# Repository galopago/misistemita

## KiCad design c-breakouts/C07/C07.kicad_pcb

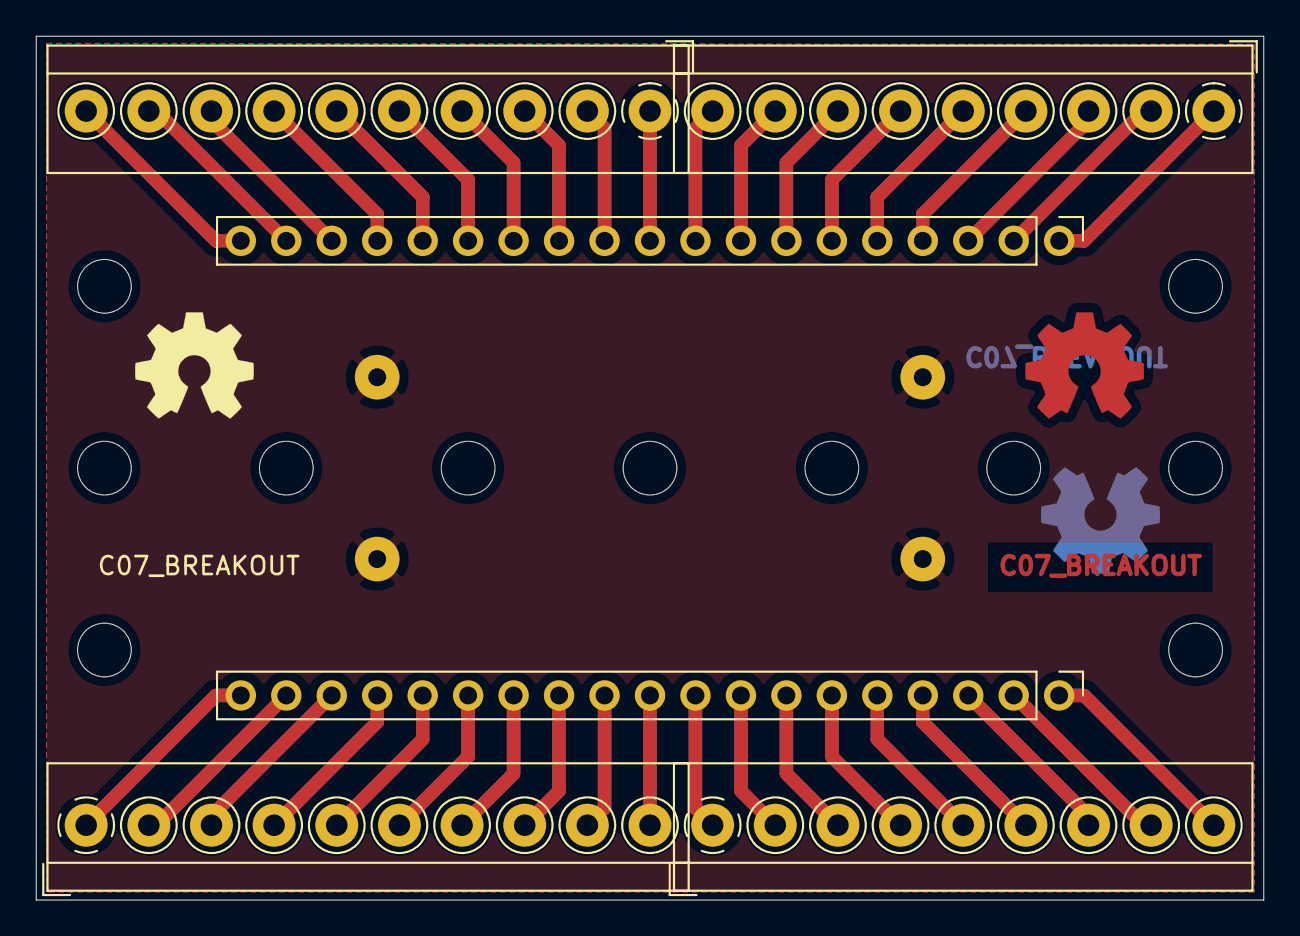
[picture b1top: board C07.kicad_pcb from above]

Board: 2 copper layers, 68.6 x 48.3 mm, 21 parts (0 on the bottom side), 39 nets.

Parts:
HB0, HB6: MountingHole; MountingHole_3mm
HC0, HC1, HC2, HC3, HC4, HC5, HC6: MountingHole; MountingHole_3mm
HD0, HD6: MountingHole; MountingHole_3mm
J0, J1, J2, J3: Conn_01x01_Male; SolderWirePad_1x01_Drill1mm
J4, J6: Conn_01x10_Female; TerminalBlock_4Ucon_1x10_P3.50mm_Horizontal
J5, J7: Conn_01x09_Female; TerminalBlock_4Ucon_1x09_P3.50mm_Horizontal
J8, J9: Conn_01x19_Female; PinHeader_1x19_P2.54mm_Vertical

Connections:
unnamed: J0.1, J1.1, J2.1, J3.1
unnamed: J4.1, J8.10
unnamed: J4.2, J8.11
unnamed: J4.3, J8.12
unnamed: J4.4, J8.13
unnamed: J4.5, J8.14
unnamed: J4.6, J8.15
unnamed: J4.7, J8.16
unnamed: J4.8, J8.17
unnamed: J4.9, J8.18
unnamed: J4.10, J8.19
unnamed: J5.1, J8.1
unnamed: J5.2, J8.2
unnamed: J5.3, J8.3
unnamed: J5.4, J8.4
unnamed: J5.5, J8.5
unnamed: J5.6, J8.6
unnamed: J5.7, J8.7
unnamed: J5.8, J8.8
unnamed: J5.9, J8.9
unnamed: J6.1, J9.19
unnamed: J6.2, J9.18
unnamed: J6.3, J9.17
unnamed: J6.4, J9.16
unnamed: J6.5, J9.15
unnamed: J6.6, J9.14
unnamed: J6.7, J9.13
unnamed: J6.8, J9.12
unnamed: J6.9, J9.11
unnamed: J6.10, J9.10
unnamed: J7.1, J9.9
unnamed: J7.2, J9.8
unnamed: J7.3, J9.7
unnamed: J7.4, J9.6
unnamed: J7.5, J9.5
unnamed: J7.6, J9.4
unnamed: J7.7, J9.3
unnamed: J7.8, J9.2
unnamed: J7.9, J9.1

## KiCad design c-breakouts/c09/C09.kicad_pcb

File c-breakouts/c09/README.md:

# Breakout for USB A female connected to a 3.5 mm pitch screw terminals (power terminals), 4 holes 10.16 mm spaced, for mounting onto the backplate.

Breakout for USB A female connected to a 3.5 mm pitch screw terminals (power terminals), 4 holes 10.16 mm spaced, for mounting onto the backplate. Useful to power modules that only have USB connector for power, but no header pins. (Using a suitable cable)

Bare single PCB                              |Panelized PCB                              |
---------------------------------------------|-------------------------------------------|
 | |

Connectors installed                         |Set attached to a 10.16 pitch backplate    |
---------------------------------------------|-------------------------------------------|
 | |

## Usage example #1

ESP32 connected to a LiFePo4 charger to send a message when charging ends. For this example the module is powered from the USB connector, therefore a breakout is needed.

Components required                                 |Ready to enclose                                 |
----------------------------------------------------|-------------------------------------------------|
||

Installed in box                             |Lid Closed                                           |
---------------------------------------------|-----------------------------------------------------|
||

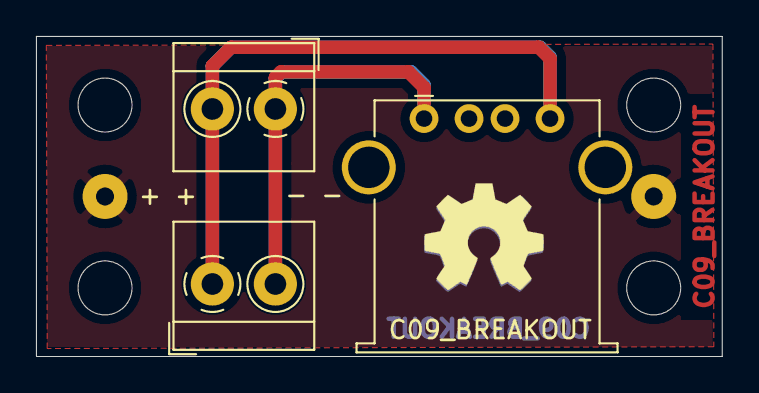
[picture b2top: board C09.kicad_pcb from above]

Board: 2 copper layers, 38.1 x 17.8 mm, 9 parts (0 on the bottom side), 3 nets.

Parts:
HA0, HA3: MountingHole; MountingHole_3mm
HB0, HB3: MountingHole; MountingHole_3mm
J0, J1: Conn_01x01_Male; SolderWirePad_1x01_Drill1mm
J4: USB_A; USB_A_Stewart_SS-52100-001_Horizontal
J5, J6: Conn_01x02_Female; TerminalBlock_4Ucon_1x02_P3.50mm_Horizontal

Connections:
unnamed: J0.1, J1.1
unnamed: J4.1, J5.1, J6.2
unnamed: J4.4, J5.2, J6.1

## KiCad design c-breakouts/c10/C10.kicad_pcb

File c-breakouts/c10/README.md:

# Breakout for I2C 0.96" OLED Display, 6 holes 10.16 mm spaced, for mounting onto the backplate.

Breakout for I2C 0.96" OLED Display, 6 holes 10.16 mm spaced, for mounting onto the backplate. Also suitable for other I2C 4-pin modules.

Bare single PCB                              |Panelized PCB                              |
---------------------------------------------|-------------------------------------------|
 | |

Connectors installed                         |Module and breakboard                      |
---------------------------------------------|-------------------------------------------|
 | |

Module attached to breakboard                |Set attached to a 10.16 pitch backplate    |
---------------------------------------------|-------------------------------------------|
 | |

## Usage example #1

ESP32 WiFi temperature probe with local display, Powered by 5V

Components required                                 |Ready to enclose                                 |
----------------------------------------------------|-------------------------------------------------|
||

Installed in box                             |Lid Closed                                       |
---------------------------------------------|-------------------------------------------------|
||

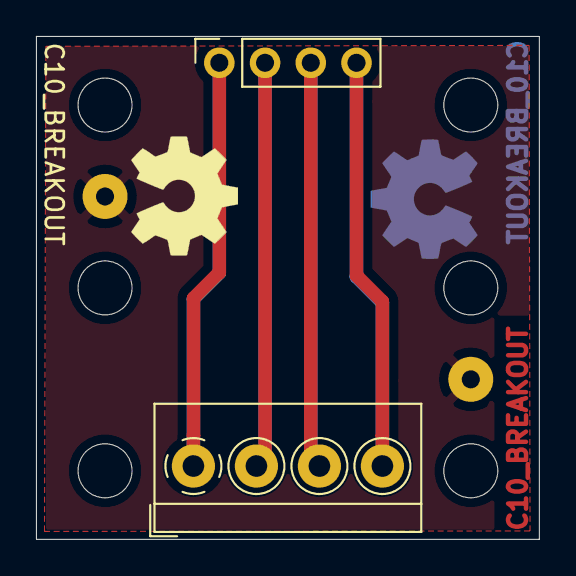
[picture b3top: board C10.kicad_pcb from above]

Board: 2 copper layers, 27.9 x 27.9 mm, 10 parts (0 on the bottom side), 5 nets.

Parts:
HA0, HA2: MountingHole; MountingHole_3mm
HB0, HB2: MountingHole; MountingHole_3mm
HC0, HC2: MountingHole; MountingHole_3mm
J0, J1: Conn_01x01_Male; SolderWirePad_1x01_Drill1mm
J4: Conn_01x04_Female; PinSocket_1x04_P2.54mm_Vertical
J5: Conn_01x04_Female; TerminalBlock_4Ucon_1x04_P3.50mm_Horizontal

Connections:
unnamed: J0.1, J1.1
unnamed: J4.1, J5.1
unnamed: J4.2, J5.2
unnamed: J4.3, J5.3
unnamed: J4.4, J5.4

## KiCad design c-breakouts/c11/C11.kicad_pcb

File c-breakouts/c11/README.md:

# Breakboard for Raspberry Pi Pico, 4 holes 10.16 mm spaced, for mounting onto the backplate

Breakboard for Raspberry Pi Pico, 4 holes 10.16 mm spaced, for mounting onto the backplate. All pins routed to 3.5 mm pitch screw terminals

Bare single PCB                              |Panelized PCB                              |
---------------------------------------------|-------------------------------------------|
 | |

Connectors installed                         |Module and breakboard                      |
---------------------------------------------|-------------------------------------------|
 | |

Module attached to breakboard                |Set attached to a 10.16 pitch backplate    |
---------------------------------------------|-------------------------------------------|
 | |

## Usage example #1

Raspberry Pi Pico based USB foot pedal. Detachable external pedals and USB cable.

Module on backplate                                 |Ready to enclose                                 |
----------------------------------------------------|-------------------------------------------------|
||

Installed in box                             |Lid Closed                                       |
---------------------------------------------|-------------------------------------------------|
||

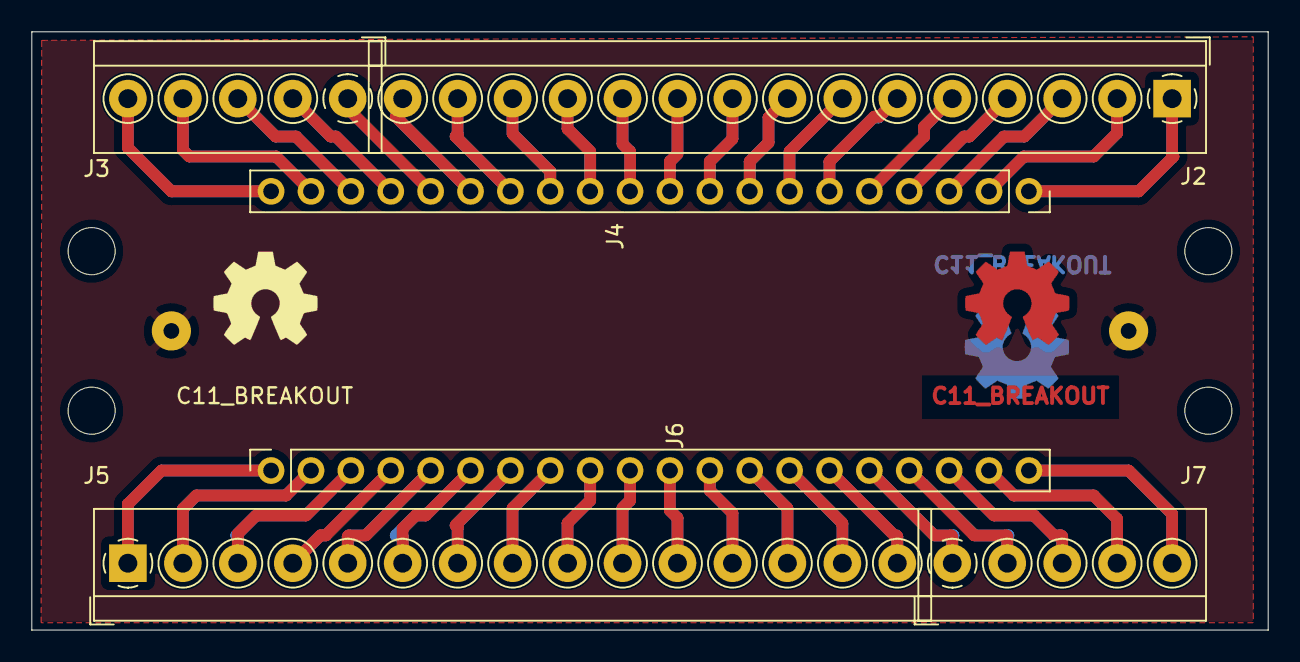
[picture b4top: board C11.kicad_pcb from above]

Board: 2 copper layers, 78.7 x 38.1 mm, 12 parts (0 on the bottom side), 41 nets.

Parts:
HB0, HB5: MountingHole; MountingHole_3mm
HC0, HC5: MountingHole; MountingHole_3mm
J0, J1: Conn_01x01_Male; SolderWirePad_1x01_Drill1mm
J2, J5: Conn_01x15_Female; TerminalBlock_4Ucon_1x15_P3.50mm_Horizontal
J3, J7: Conn_01x05_Female; TerminalBlock_4Ucon_1x05_P3.50mm_Horizontal
J4, J6: Conn_01x20_Female; PinSocket_1x20_P2.54mm_Vertical

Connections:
unnamed: J0.1, J1.1
unnamed: J2.1, J4.1
unnamed: J2.2, J4.2
unnamed: J2.3, J4.3
unnamed: J2.4, J4.4
unnamed: J2.5, J4.5
unnamed: J2.6, J4.6
unnamed: J2.7, J4.7
unnamed: J2.8, J4.8
unnamed: J2.9, J4.9
unnamed: J2.10, J4.10
unnamed: J2.11, J4.11
unnamed: J2.12, J4.12
unnamed: J2.13, J4.13
unnamed: J2.14, J4.14
unnamed: J2.15, J4.15
unnamed: J3.1, J4.16
unnamed: J3.2, J4.17
unnamed: J3.3, J4.18
unnamed: J3.4, J4.19
unnamed: J3.5, J4.20
unnamed: J5.1, J6.1
unnamed: J5.2, J6.2
unnamed: J5.3, J6.3
unnamed: J5.4, J6.4
unnamed: J5.5, J6.5
unnamed: J5.6, J6.6
unnamed: J5.7, J6.7
unnamed: J5.8, J6.8
unnamed: J5.9, J6.9
unnamed: J5.10, J6.10
unnamed: J5.11, J6.11
unnamed: J5.12, J6.12
unnamed: J5.13, J6.13
unnamed: J5.14, J6.14
unnamed: J5.15, J6.15
unnamed: J6.16, J7.1
unnamed: J6.17, J7.2
unnamed: J6.18, J7.3
unnamed: J6.19, J7.4
unnamed: J6.20, J7.5

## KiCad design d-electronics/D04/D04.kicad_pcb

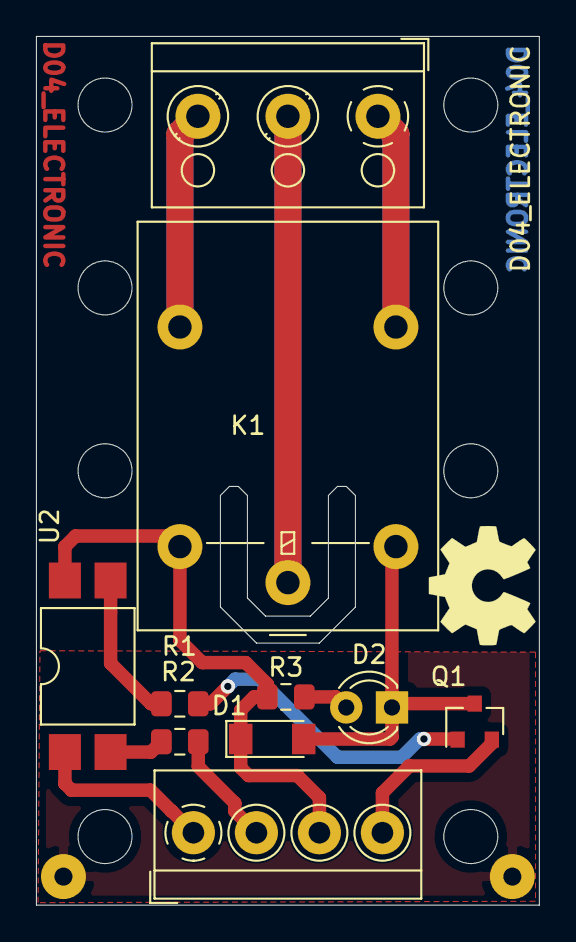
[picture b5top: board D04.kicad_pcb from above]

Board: 2 copper layers, 27.9 x 48.3 mm, 20 parts (0 on the bottom side), 13 nets.

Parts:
D1: LL4148; D_MiniMELF
D2: LED; LED_D3.0mm
HA0, HA2: MountingHole; MountingHole_3mm
HB0, HB2: MountingHole; MountingHole_3mm
HC0, HC2: MountingHole; MountingHole_3mm
HE0, HE2: MountingHole; MountingHole_3mm
J0, J1: Conn_01x01_Male; SolderWirePad_1x01_Drill1mm
J4: Conn_01x03_Female; TerminalBlock_RND_205-00002_1x03_P5.00mm_Horizontal
J5: Conn_01x04_Female; TerminalBlock_4Ucon_1x04_P3.50mm_Horizontal
K1: G5LE-1; Relay_SPDT_Omron-G5LE-1
Q1: MMBT3904; SOT-23
R1, R2, R3: R; R_0805_2012Metric_Pad1.15x1.40mm_HandSolder
U2: LTV-817S; SMDIP-4_W9.53mm

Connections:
unnamed: D1.1, J5.3, K1.5, R3.1, U2.4
unnamed: D1.2, D2.1, K1.2, Q1.3
unnamed: D2.2, R3.2
unnamed: J0.1, J1.1
unnamed: J4.1, K1.3
unnamed: J4.2, K1.1
unnamed: J4.3, K1.4
unnamed: J5.1, U2.1
unnamed: J5.2, R2.1
unnamed: J5.4, Q1.2
unnamed: Q1.1, R1.1
unnamed: R1.2, U2.3
unnamed: R2.2, U2.2
